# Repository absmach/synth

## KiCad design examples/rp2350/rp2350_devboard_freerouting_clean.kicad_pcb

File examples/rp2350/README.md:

# RP2350 routed example

## Latest regenerated run

The full-board reconstruction routes with the installed FreeRouting pipeline
on six layers. Local generated artifacts are under
`reproductions/rp2350-reconstructed/generated/`:

- `rp2350_devboard_reconstructed.synth` — reconstructed Synth source
- `rp2350_devboard_reconstructed.layout.toml` — recovered placement sidecar
- `rp2350_devboard_freerouted_6layer.kicad_pcb` — routed KiCad board
- `rp2350_devboard_freerouted_6layer.png` — rendered review image
- `freerouted-6layer-drc.rpt` — native KiCad DRC report

FreeRouting completed with **0 unrouted signal nets**. The DRC report still
contains 14 ground-zone island items and two footprint-library warnings; this
is not production sign-off until those items are reviewed.

`rp2350_devboard_freerouting_clean.kicad_pcb` is a pre-generated compact KiCad
review artifact.

Reference dimensions: approximately **84.5 × 73.1 mm**.

Open the [KiCad board](rp2350_devboard_freerouting_clean.kicad_pcb) for an
interactive review.

The companion DRC report records the current review state. The authoritative
KiCad check currently reports **80 DRC violations** and **18 unconnected
items**. The 18 unconnected entries are zone-to-zone ground-island reports,
not ordinary signal-pad pairs, but they are still violations. This is an
example and review fixture, not production sign-off; silkscreen and footprint
library warnings also require engineering review.

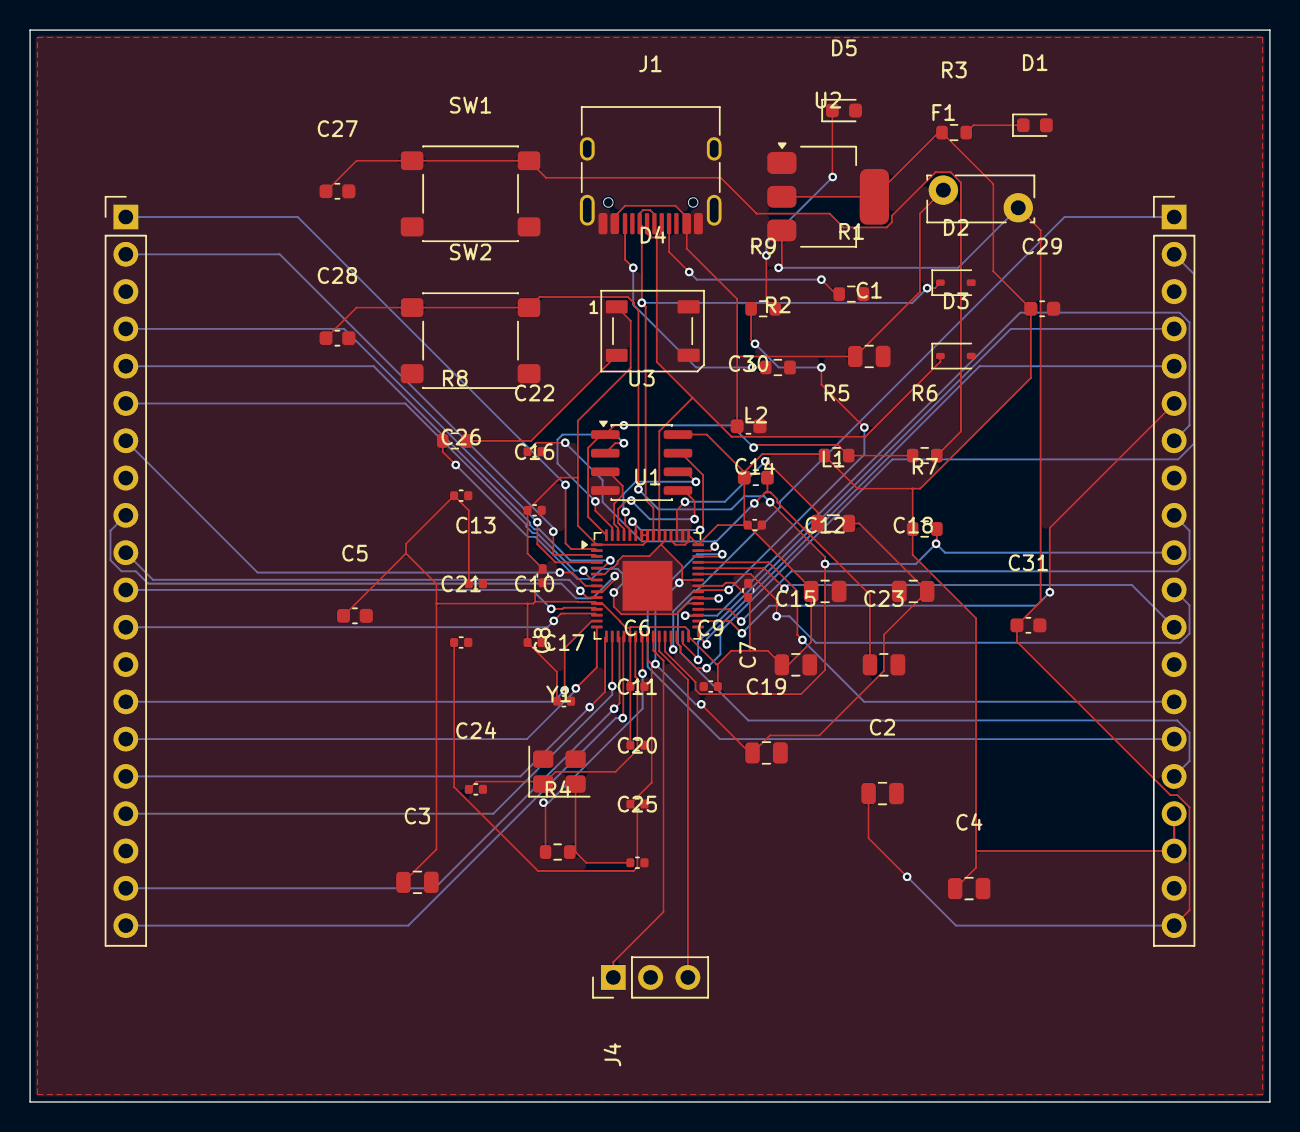
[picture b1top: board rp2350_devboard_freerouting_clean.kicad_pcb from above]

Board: 4 copper layers, 84.4 x 73.0 mm, 58 parts (0 on the bottom side), 57 nets.

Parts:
C1, C2, C3, C4, C12, C15, C18, C19, C23: c_generic_0805; C_0805_2012Metric
C5, C27, C28, C29, C30, C31: c_generic_0603; C_0603_1608Metric
C6, C7, C8, C9, C10, C11, C13, C14, C16, C17, C20, C21, C22, C24, C25, C26: c_generic_0402; C_0402_1005Metric
D1: led_green_0603; LED_0603_1608Metric
D2, D3: esd_usb; D_SOD-323
D4: ws2812b_5050; LED_WS2812B_PLCC4_5.0x5.0mm_P3.2mm
D5: led_red_0603; LED_0603_1608Metric
F1: polyfuse; Fuse_Bourns_MF-RG300
J1: usb_c_receptacle; USB_C_Receptacle_HRO_TYPE-C-31-M-12
J2, J3: header_1x20; PinHeader_1x20_P2.54mm_Vertical
J4: header_1x3; PinHeader_1x03_P2.54mm_Vertical
L1: l_generic_0805; L_0805_2012Metric
L2: ferrite_bead_0603; L_0603_1608Metric
R1, R2, R3, R4, R5, R6, R7, R8, R9: r_generic_0603; R_0603_1608Metric
SW1, SW2: spst_tactile; SW_SPST_PTS645Sx43SMTR92
U1: rp2350a; QFN-60-1EP_7x7mm_P0.4mm_EP3.4x3.4mm
U2: ams1117_3v3; SOT-223-3_TabPin2
U3: w25q128_qspi; SOIC-8_3.9x4.9mm_P1.27mm
Y1: xtal_generic; Crystal_SMD_3225-4Pin_3.2x2.5mm

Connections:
net_0: J1.A5, R1.1
net_1: C1.2, C2.2, C3.2, C4.2, C5.2, C6.2, C7.2, C8.2, C9.2, C10.2, C11.2, C12.2, C13.2, C14.2, C15.2, C16.2, C17.2, C18.2, C19.2, C20.2, C21.2, C22.2, C23.2, C24.2, C25.2, C26.2, C27.2, C28.2, C29.2, C30.2, C31.2, D1.2, D2.2, D3.2, D4.3, D4.4, D5.2, J1.A1, J1.A12, J1.B1, J1.B12, J1.SH, J2.3, J2.8, J2.13, J2.18, J3.3, J3.8, J3.13, J3.19, J4.2, R1.2, R2.2, SW1.2, SW2.2, U1.47, U1.61, U2.1, U3.4
net_2: J1.B5, R2.1
net_3: C1.1, C30.1, F1.1, J1.A4, J1.A9, J1.B4, J1.B9
net_4: C2.1, C31.1, F1.2, J3.20, U2.3
net_5: C3.1, C4.1, C5.1, C6.1, C7.1, C8.1, C9.1, C10.1, C11.1, C12.1, C13.1, C14.1, C15.1, C16.1, C17.1, C26.1, C29.1, D4.1, J3.17, J3.18, L2.1, R3.1, R5.1, R7.1, U1.1, U1.11, U1.20, U1.30, U1.38, U1.45, U1.46, U1.49, U1.53, U1.54, U2.2, U3.8
net_6: D1.1, R3.2
net_7: L1.1, U1.48
net_8: C18.1, C19.1, C20.1, C21.1, L1.2, U1.6, U1.23, U1.39, U1.50
net_9: C22.1, C23.1, L2.2, U1.44
net_10: C24.1, U1.21, Y1.1
net_11: R4.1, U1.22
net_12: C25.1, R4.2, Y1.2
net_13: R5.2, R6.1, U1.60, U3.1
net_14: U1.56, U3.6
net_15: U1.57, U3.5
net_16: U1.59, U3.2
net_17: U1.58, U3.3
net_18: U1.55, U3.7
net_19: C27.1, R6.2, SW1.1
net_20: C28.1, J3.10, R7.2, SW2.1, U1.26
net_21: D2.1, J1.A6, J1.B6, U1.52
net_22: D3.1, J1.A7, J1.B7, U1.51
net_23: R8.1, U1.35
net_24: D4.2, R8.2
net_25: R9.1, U1.37
net_26: D5.1, R9.2
net_27: J4.1, U1.24
net_28: J4.3, U1.25
net_29: J2.1, U1.2
net_30: J2.2, U1.3
net_31: J2.4, U1.4
net_32: J2.5, U1.5
net_33: J2.6, U1.7
net_34: J2.7, U1.8
net_35: J2.9, U1.9
net_36: J2.10, U1.10
net_37: J2.11, U1.12
net_38: J2.12, U1.13
net_39: J2.14, U1.14
net_40: J2.15, U1.15
net_41: J2.16, U1.16
net_42: J2.17, U1.17
net_43: J2.19, U1.18
net_44: J2.20, U1.19
net_45: J3.1, U1.27
net_46: J3.2, U1.28
net_47: J3.4, U1.29
net_48: J3.5, U1.31
net_49: J3.6, U1.32
net_50: J3.7, U1.33
net_51: J3.9, U1.34
net_52: J3.11, U1.40
net_53: J3.12, U1.41
net_54: J3.14, U1.42
net_55: J3.15, U1.43
net_56: J3.16, U1.36

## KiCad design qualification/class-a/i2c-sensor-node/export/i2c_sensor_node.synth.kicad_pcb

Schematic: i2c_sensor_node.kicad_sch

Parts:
C1, C2, C4: 10uF; C_0805_2012Metric
C3: 47uF; CP_EIA-3528-21_Kemet-B
C5, C6, C8, C10, C11, C12: 100nF; C_0603_1608Metric
C7: 4.7uF; C_0603_1608Metric
D1, D14: 1N5819; D_SOD-123; MPN 1N5819HW-7-F; LCSC C82544
D4: PTVS6V0S1UR; Nexperia_CFP3_SOD-123W; MPN PTVS6V0S1UR
D7, D8, D9, D10, D11, D12, D13, D19, D20, D21, D22, D23, D24: 3.3V zener; D_SOD-123
D15: GREEN; LED_0603_1608Metric; MPN LTST-C190KGKT
F1: 0.5A hold; Fuse_1812_4532Metric
H2, H3: (no value); MountingHole_2.5mm
J1: JST S2B-XH-A-1; JST_XH_S2B-XH-A-1_1x02_P2.50mm_Horizontal
J3: JST S4B-PH-K-S; JST_PH_S4B-PH-K_1x04_P2.00mm_Horizontal
J4: SWD; PinHeader_1x05_P2.54mm_Vertical
J5: GPIO; PinHeader_1x12_P2.54mm_Vertical
R3: 10k; R_0603_1608Metric
R9, R10: 4.7k; R_0603_1608Metric
R11, R15, R16, R17, R18, R19, R20, R21, R22: 330; R_0603_1608Metric
R12: 1k; R_0603_1608Metric
R13, R14: 100; R_0603_1608Metric
R23: 100; R_0805_2012Metric
R24: 680; R_0603_1608Metric
SW1: RESET; SW_SPST_PTS645Sx43SMTR92
U1: AMS1117-3.3; SOT-223-3_TabPin2; MPN AMS1117-3.3; LCSC C6186
U2: STM32G030F6P6; TSSOP-20_4.4x6.5mm_P0.65mm; MPN STM32G030F6P6
U3: BME680; Bosch_LGA-8_3x3mm_P0.8mm_ClockwisePinNumbering; MPN BME680
U5: 24LC256-I/SN; SOIC-8_3.9x4.9mm_P1.27mm; MPN 24LC256-I/SN; LCSC C411625

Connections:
3V3_REF: J3.4, J4.1, J5.1, R23.2
+3V3: C3.1, C4.1, C5.1, C6.1, C7.1, C10.1, C11.1, C12.1, D14.2 (A), R3.1, R9.1, R10.1, R24.1, U1.2 (VO), U2.4 (VDD), U3.2 (CSB), U3.6 (VDDIO), U3.8 (VDD), U5.8 (VCC)
+5V_PROT: C1.1, C2.1, D1.1 (K), D4.1 (K), U1.3 (VI)
GND: C1.2, C2.2, C3.2, C4.2, C5.2, C6.2, C7.2, C8.2, C10.2, C11.2, C12.2, D4.2 (A), D7.2 (A), D8.2 (A), D9.2 (A), D10.2 (A), D11.2 (A), D12.2 (A), D13.2 (A), D15.1 (K), D19.2 (A), D20.2 (A), D21.2 (A), D22.2 (A), D23.2 (A), D24.2 (A), J1.2, J3.1, J4.4, J5.2, J5.6, J5.10, SW1.2, U1.1 (GND), U2.5 (VSS), U3.1 (GND), U3.5 (SDO), U3.7 (GND), U5.1 (A0), U5.2 (A1), U5.3 (A2), U5.4 (GND), U5.7 (WP)
GPIO_PA0: J5.3, R15.2
GPIO_PA0_MCU: D10.1 (K), R15.1, U2.7 (PA0)
GPIO_PA1: J5.4, R16.2
GPIO_PA1_MCU: D20.1 (K), R16.1, U2.8 (PA1)
GPIO_PA4: J5.5, R17.2
GPIO_PA4_MCU: D11.1 (K), R17.1, U2.11 (PA4)
GPIO_PA5: J5.7, R18.2
GPIO_PA5_MCU: D21.1 (K), R18.1, U2.12 (PA5)
GPIO_PA6: J5.8, R19.2
GPIO_PA6_MCU: D12.1 (K), R19.1, U2.13 (PA6)
GPIO_PA7: J5.9, R20.2
GPIO_PA7_MCU: D22.1 (K), R20.1, U2.14 (PA7)
GPIO_PB0: J5.11, R21.2
GPIO_PB0_MCU: D13.1 (K), R21.1, U2.15 (PA8/PB0/PB1/PB2)
GPIO_PB9: J5.12, R22.2
GPIO_PB9_MCU: D23.1 (K), R22.1, U2.2 (PB9/PC14)
I2C_SCL: R10.2, U2.20 (PB3/PB4/PB5/PB6), U3.4 (SCK), U5.6 (SCL)
I2C_SDA: R9.2, U2.1 (PB7/PB8), U3.3 (SDI), U5.5 (SDA)
LED_PWR: D15.2 (A), R24.2
NRST: C8.1, D19.1 (K), J4.5, R3.2, SW1.1, U2.6 (NRST)
REF_D: D14.1 (K), R23.1
SWCLK: D9.1 (K), J4.3, R14.2
SWCLK_MCU: R14.1, U2.19 (PA14/PA15)
SWDIO: D8.1 (K), J4.2, R13.2
SWDIO_MCU: R13.1, U2.18 (PA13)
U2_RX: D24.1 (K), R12.1, U2.10 (PA3)
U2_TX: D7.1 (K), R11.1, U2.9 (PA2)
UART_RX: J3.3, R12.2
UART_TX: J3.2, R11.2
VIN_5V_FUSED: D1.2 (A), F1.2
VIN_5V_RAW: F1.1, J1.1

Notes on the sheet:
5V INPUT: FUSE THEN DIODE
3V3 REGULATOR
STM32G030 MCU
I2C SENSING
UART BREAKOUT
GPIO HEADER
MOUNTING
J1 pin 1 = +5 V, pin 2 = GND (JST XHP-2). Fuse first, then the
reverse-polarity diode D1.
D4 clamps transients on +5V_PROT, behind D1 so a reversed supply never
forward-biases it.
AMS1117 tab is VOUT. Load budget 100 mA: P = (5.0 - 3.3) x 0.1 A =
0.17 W, thetaJA 90 C/W gives a 15 C rise (125 C limit).
LED (VF 1.9 to 2.4 V): 1.3 to 2.1 mA through 680 R. C3 is 47 uF
tantalum (22 uF required).
J4: 1 = 3V3_REF, 2 = SWDIO, 3 = SWCLK, 4 = GND, 5 = NRST. PA14 is
SWCLK and BOOT0.
D8, D9, D19 are 3.3 V zeners; a 5 V fault through 100 R is (5 - 3.3) /
100 = 17 mA, 56 mW.
BME680 SDO low = 0x76, CSB high = I2C. 24LC256 A2:A0 low = 0x50. No
collision.
One pull-up pair, 4.7k each, for the whole bus.
J3: 1 GND, 2 UART_TX, 3 UART_RX, 4 3V3_REF (3 mA max). Host logic 3.3
V to 5 V.
D7, D24 are 3.3 V zeners behind 330 R and 1 k: a 5 V fault is 5.2 mA
(17 mW) and 1.7 mA (5.6 mW).
J5: 1 3V3_REF, 2 GND, 3 PA0, 4 PA1, 5 PA4, 6 GND, 7 PA5, 8 PA6, 9 PA7,
10 GND, 11 PB0, 12 PB9.
D10..D13, D20..D23: one 3.3 V zener per line behind 330 R; a 5 V fault
is 5.2 mA, 17 mW. 3V3_REF is +3V3 through D14 and 100 R, 3 mA max.
H2, H3: two M2.5 non-plated mounting holes at opposite (diagonal)
corners.

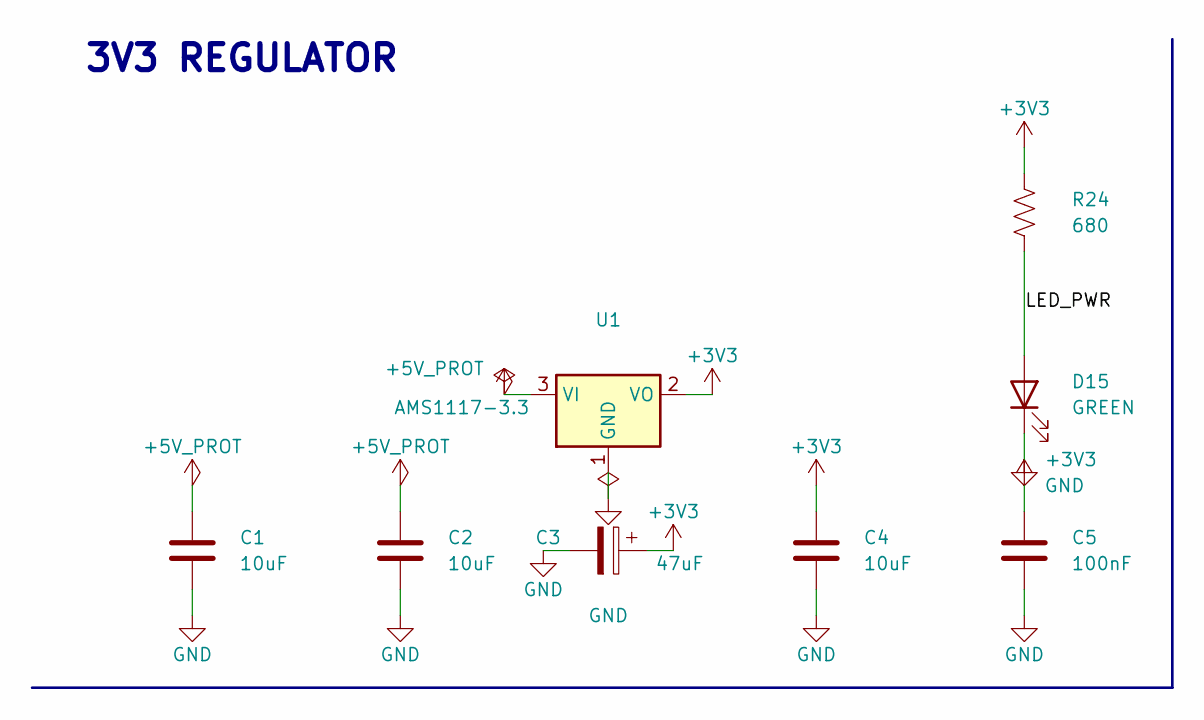
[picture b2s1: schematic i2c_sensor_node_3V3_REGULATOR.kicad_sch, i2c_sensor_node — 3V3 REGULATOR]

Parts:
C1, C2, C4: 10uF; C_0805_2012Metric
C3: 47uF; CP_EIA-3528-21_Kemet-B
C5: 100nF; C_0603_1608Metric
D15: GREEN; LED_0603_1608Metric; MPN LTST-C190KGKT
R24: 680; R_0603_1608Metric
U1: AMS1117-3.3; SOT-223-3_TabPin2; MPN AMS1117-3.3; LCSC C6186

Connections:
+3V3: C3.1, C4.1, C5.1, R24.1, U1.2 (VO); also elsewhere on the board
+5V_PROT: C1.1, C2.1, U1.3 (VI); also elsewhere on the board
GND: C1.2, C2.2, C3.2, C4.2, C5.2, D15.1 (K), U1.1 (GND); also elsewhere on the board
LED_PWR: D15.2 (A), R24.2

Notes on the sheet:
3V3 REGULATOR

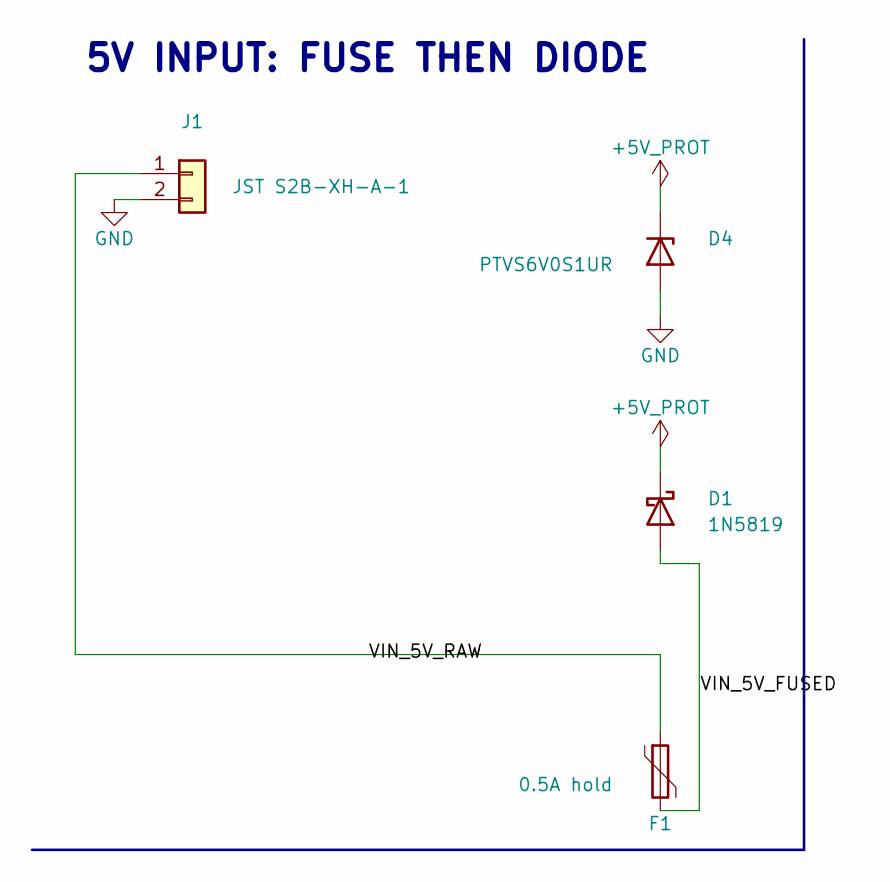
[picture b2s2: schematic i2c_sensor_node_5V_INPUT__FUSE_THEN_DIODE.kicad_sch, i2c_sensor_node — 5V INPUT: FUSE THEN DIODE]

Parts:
D1: 1N5819; D_SOD-123; MPN 1N5819HW-7-F; LCSC C82544
D4: PTVS6V0S1UR; Nexperia_CFP3_SOD-123W; MPN PTVS6V0S1UR
F1: 0.5A hold; Fuse_1812_4532Metric
J1: JST S2B-XH-A-1; JST_XH_S2B-XH-A-1_1x02_P2.50mm_Horizontal

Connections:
+5V_PROT: D1.1 (K), D4.1 (K); also elsewhere on the board
GND: D4.2 (A), J1.2; also elsewhere on the board
VIN_5V_FUSED: D1.2 (A), F1.2
VIN_5V_RAW: F1.1, J1.1

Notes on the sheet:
5V INPUT: FUSE THEN DIODE

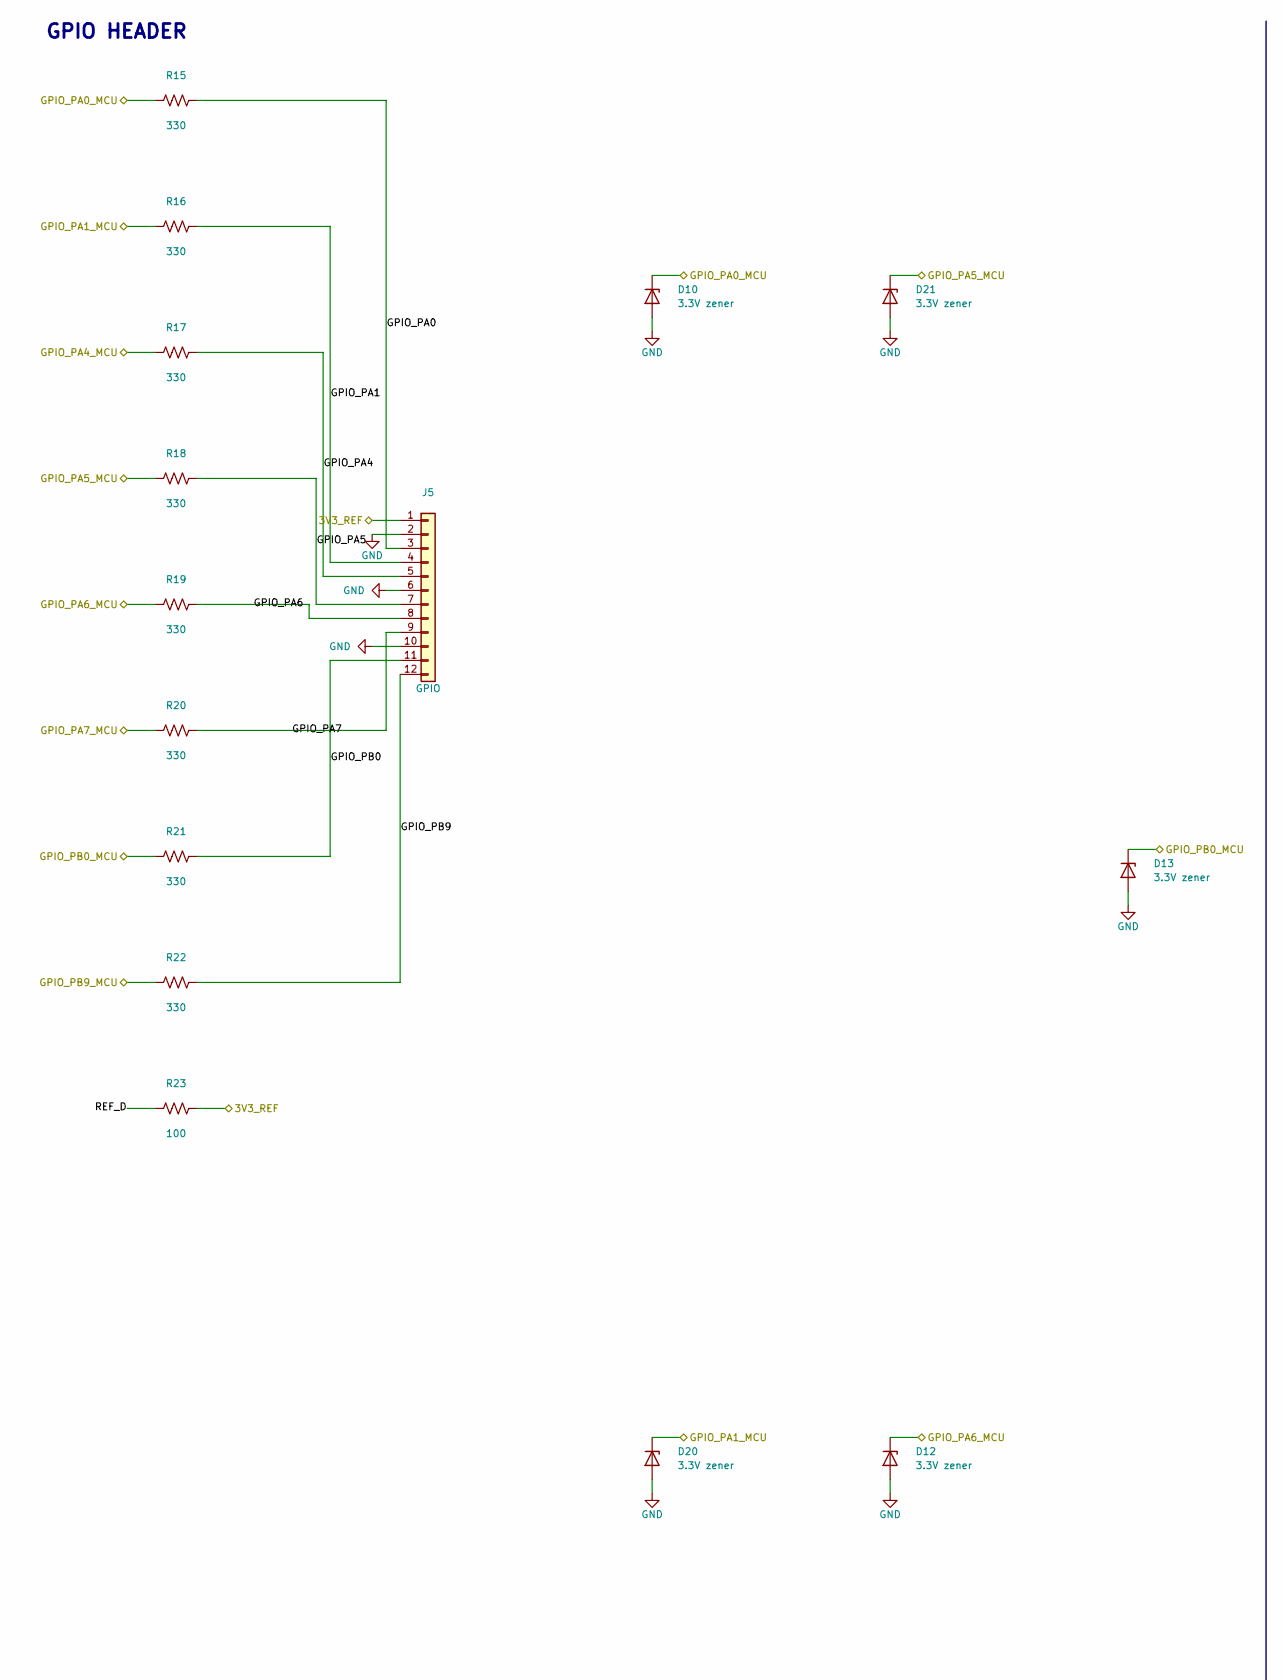
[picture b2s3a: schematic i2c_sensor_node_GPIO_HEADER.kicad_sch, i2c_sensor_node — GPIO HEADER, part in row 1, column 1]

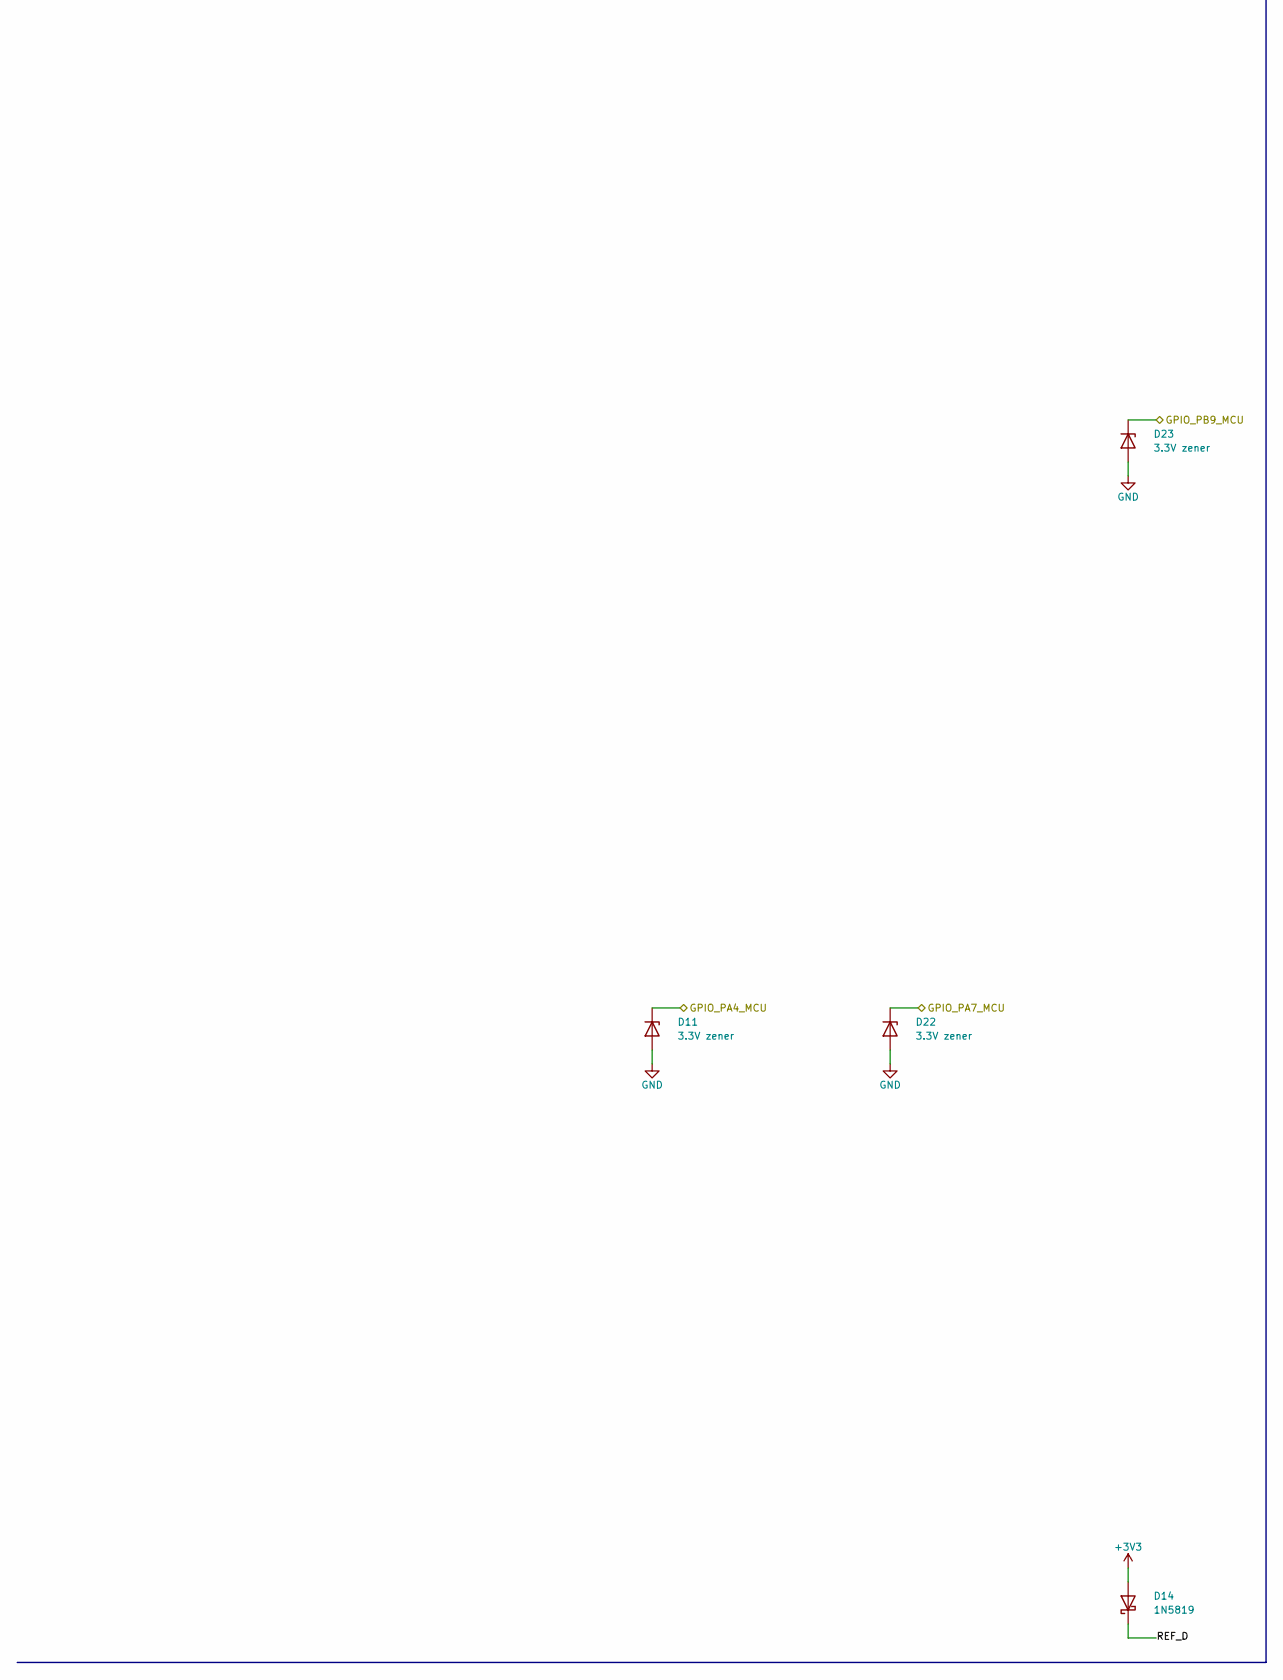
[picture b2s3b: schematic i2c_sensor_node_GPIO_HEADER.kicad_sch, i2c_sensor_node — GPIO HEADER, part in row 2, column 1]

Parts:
D10, D11, D12, D13, D20, D21, D22, D23: 3.3V zener; D_SOD-123
D14: 1N5819; D_SOD-123; MPN 1N5819HW-7-F; LCSC C82544
J5: GPIO; PinHeader_1x12_P2.54mm_Vertical
R15, R16, R17, R18, R19, R20, R21, R22: 330; R_0603_1608Metric
R23: 100; R_0805_2012Metric

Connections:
3V3_REF: J5.1, R23.2; also elsewhere on the board
+3V3: D14.2 (A); also elsewhere on the board
GND: D10.2 (A), D11.2 (A), D12.2 (A), D13.2 (A), D20.2 (A), D21.2 (A), D22.2 (A), D23.2 (A), J5.2, J5.6, J5.10; also elsewhere on the board
GPIO_PA0: J5.3, R15.2
GPIO_PA0_MCU: D10.1 (K), R15.1; also elsewhere on the board
GPIO_PA1: J5.4, R16.2
GPIO_PA1_MCU: D20.1 (K), R16.1; also elsewhere on the board
GPIO_PA4: J5.5, R17.2
GPIO_PA4_MCU: D11.1 (K), R17.1; also elsewhere on the board
GPIO_PA5: J5.7, R18.2
GPIO_PA5_MCU: D21.1 (K), R18.1; also elsewhere on the board
GPIO_PA6: J5.8, R19.2
GPIO_PA6_MCU: D12.1 (K), R19.1; also elsewhere on the board
GPIO_PA7: J5.9, R20.2
GPIO_PA7_MCU: D22.1 (K), R20.1; also elsewhere on the board
GPIO_PB0: J5.11, R21.2
GPIO_PB0_MCU: D13.1 (K), R21.1; also elsewhere on the board
GPIO_PB9: J5.12, R22.2
GPIO_PB9_MCU: D23.1 (K), R22.1; also elsewhere on the board
REF_D: D14.1 (K), R23.1

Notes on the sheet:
GPIO HEADER

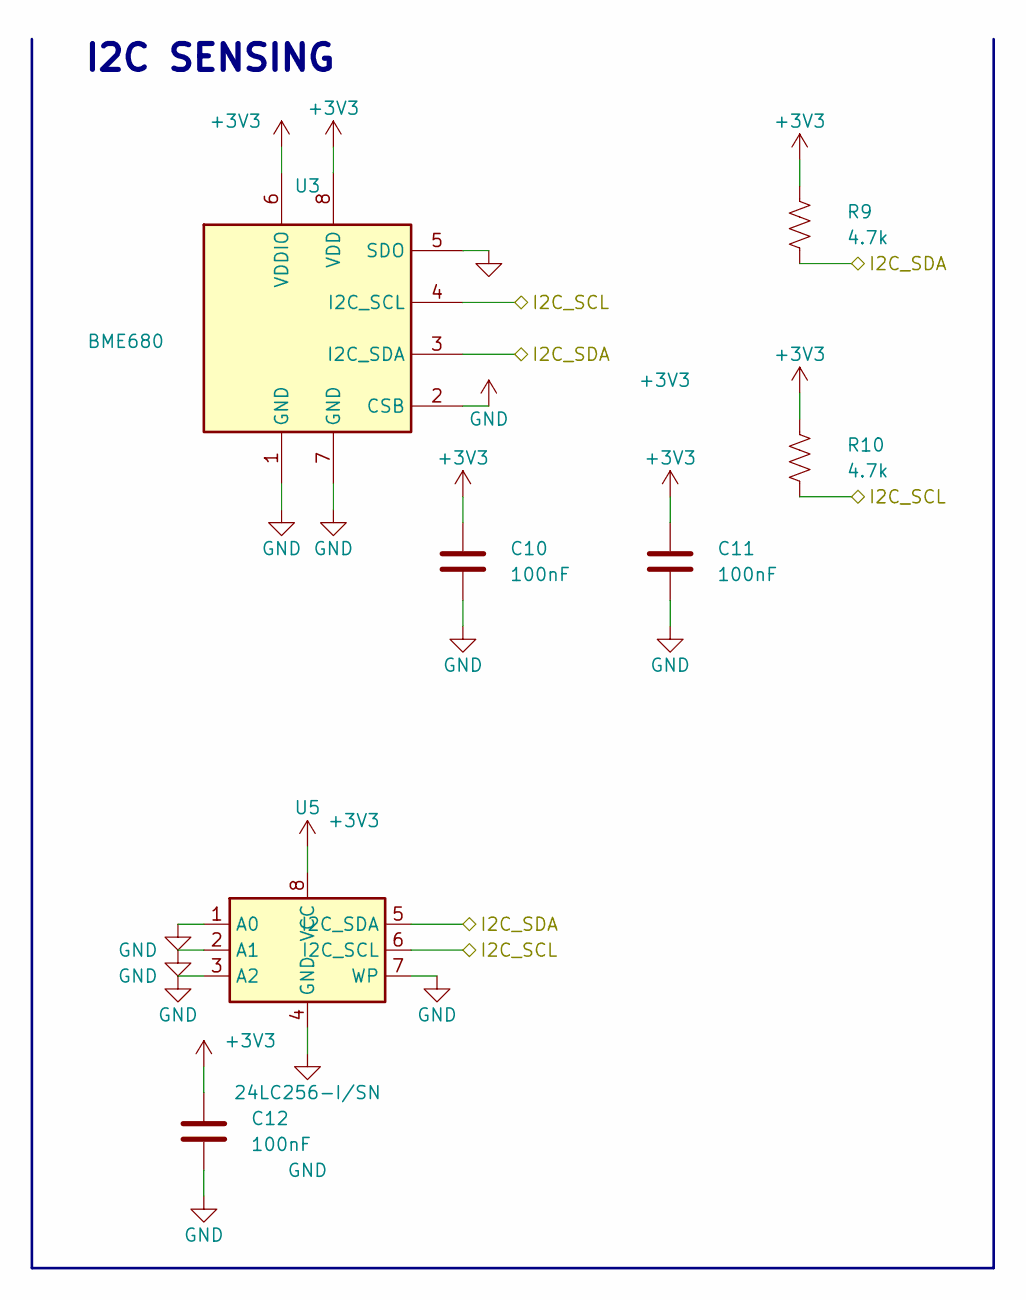
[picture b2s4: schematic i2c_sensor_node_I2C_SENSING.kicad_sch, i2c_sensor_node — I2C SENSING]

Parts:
C10, C11, C12: 100nF; C_0603_1608Metric
R9, R10: 4.7k; R_0603_1608Metric
U3: BME680; Bosch_LGA-8_3x3mm_P0.8mm_ClockwisePinNumbering; MPN BME680
U5: 24LC256-I/SN; SOIC-8_3.9x4.9mm_P1.27mm; MPN 24LC256-I/SN; LCSC C7611

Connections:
+3V3: C10.1, C11.1, C12.1, R9.1, R10.1, U3.2 (CSB), U3.6 (VDDIO), U3.8 (VDD), U5.8 (VCC); also elsewhere on the board
GND: C10.2, C11.2, C12.2, U3.1 (GND), U3.5 (SDO), U3.7 (GND), U5.1 (A0), U5.2 (A1), U5.3 (A2), U5.4 (GND), U5.7 (WP); also elsewhere on the board
I2C_SCL: R10.2, U3.4 (SCK), U5.6 (SCL); also elsewhere on the board
I2C_SDA: R9.2, U3.3 (SDI), U5.5 (SDA); also elsewhere on the board

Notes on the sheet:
I2C SENSING

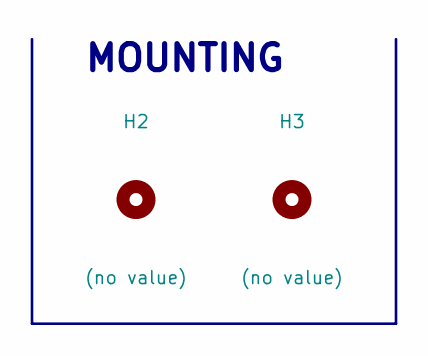
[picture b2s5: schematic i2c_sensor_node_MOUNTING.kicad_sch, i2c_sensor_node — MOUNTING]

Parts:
H2, H3: (no value); MountingHole_2.5mm

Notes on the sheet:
MOUNTING

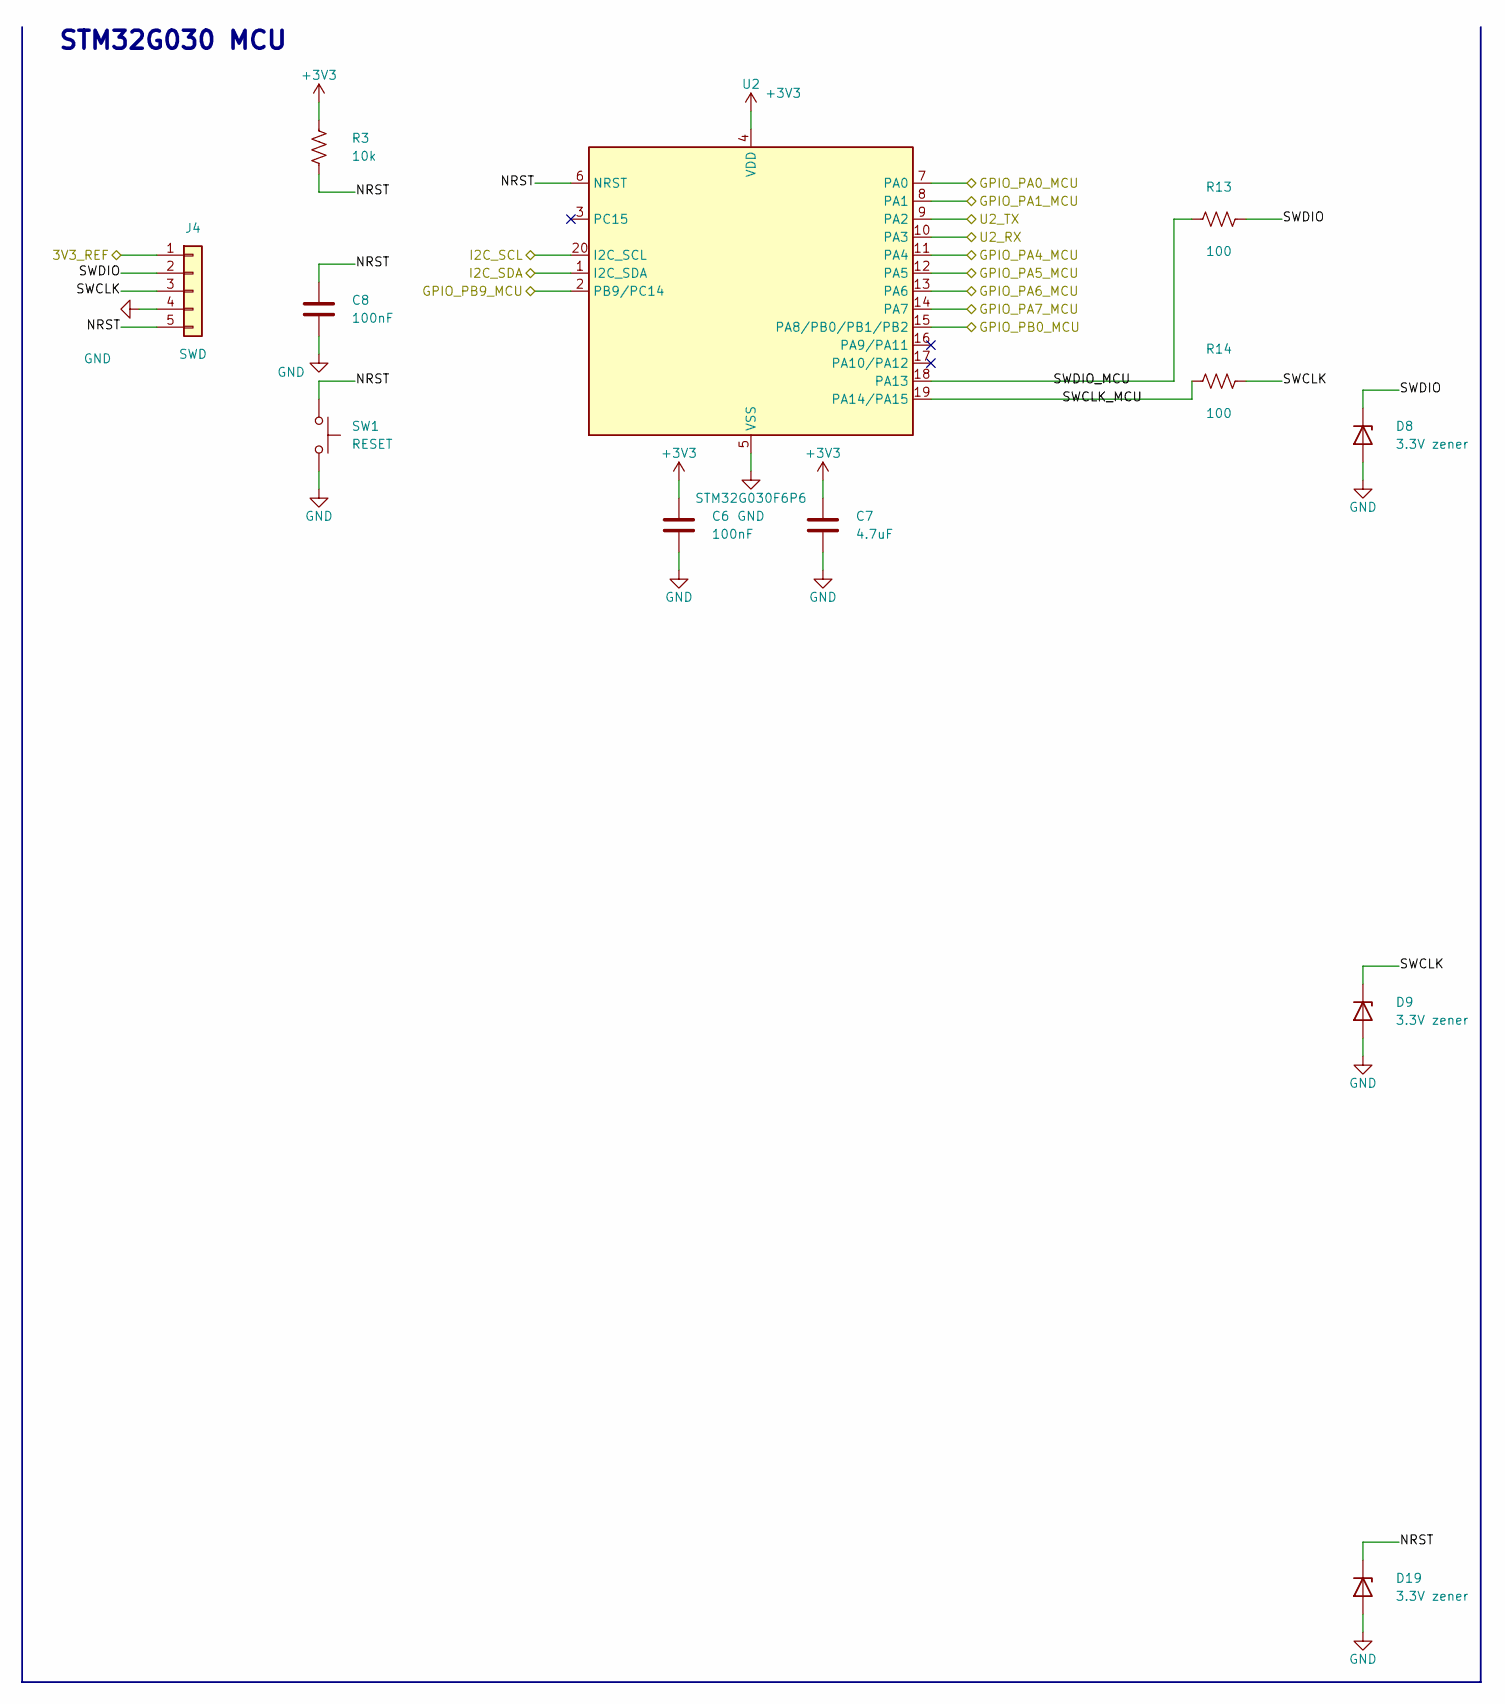
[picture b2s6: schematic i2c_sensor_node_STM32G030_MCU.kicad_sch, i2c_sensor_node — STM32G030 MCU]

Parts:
C6, C8: 100nF; C_0603_1608Metric
C7: 4.7uF; C_0603_1608Metric
D8, D9, D19: 3.3V zener; D_SOD-123
J4: SWD; PinHeader_1x05_P2.54mm_Vertical
R3: 10k; R_0603_1608Metric
R13, R14: 100; R_0603_1608Metric
SW1: RESET; SW_SPST_PTS645Sx43SMTR92
U2: STM32G030F6P6; TSSOP-20_4.4x6.5mm_P0.65mm; MPN STM32G030F6P6

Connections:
3V3_REF: J4.1; also elsewhere on the board
+3V3: C6.1, C7.1, R3.1, U2.4 (VDD); also elsewhere on the board
GND: C6.2, C7.2, C8.2, D8.2 (A), D9.2 (A), D19.2 (A), J4.4, SW1.2, U2.5 (VSS); also elsewhere on the board
GPIO_PA0_MCU: U2.7 (PA0); also elsewhere on the board
GPIO_PA1_MCU: U2.8 (PA1); also elsewhere on the board
GPIO_PA4_MCU: U2.11 (PA4); also elsewhere on the board
GPIO_PA5_MCU: U2.12 (PA5); also elsewhere on the board
GPIO_PA6_MCU: U2.13 (PA6); also elsewhere on the board
GPIO_PA7_MCU: U2.14 (PA7); also elsewhere on the board
GPIO_PB0_MCU: U2.15 (PA8/PB0/PB1/PB2); also elsewhere on the board
GPIO_PB9_MCU: U2.2 (PB9/PC14); also elsewhere on the board
I2C_SCL: U2.20 (PB3/PB4/PB5/PB6); also elsewhere on the board
I2C_SDA: U2.1 (PB7/PB8); also elsewhere on the board
NRST: C8.1, D19.1 (K), J4.5, R3.2, SW1.1, U2.6 (NRST)
SWCLK: D9.1 (K), J4.3, R14.2
SWCLK_MCU: R14.1, U2.19 (PA14/PA15)
SWDIO: D8.1 (K), J4.2, R13.2
SWDIO_MCU: R13.1, U2.18 (PA13)
U2_RX: U2.10 (PA3); also elsewhere on the board
U2_TX: U2.9 (PA2); also elsewhere on the board

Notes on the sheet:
STM32G030 MCU

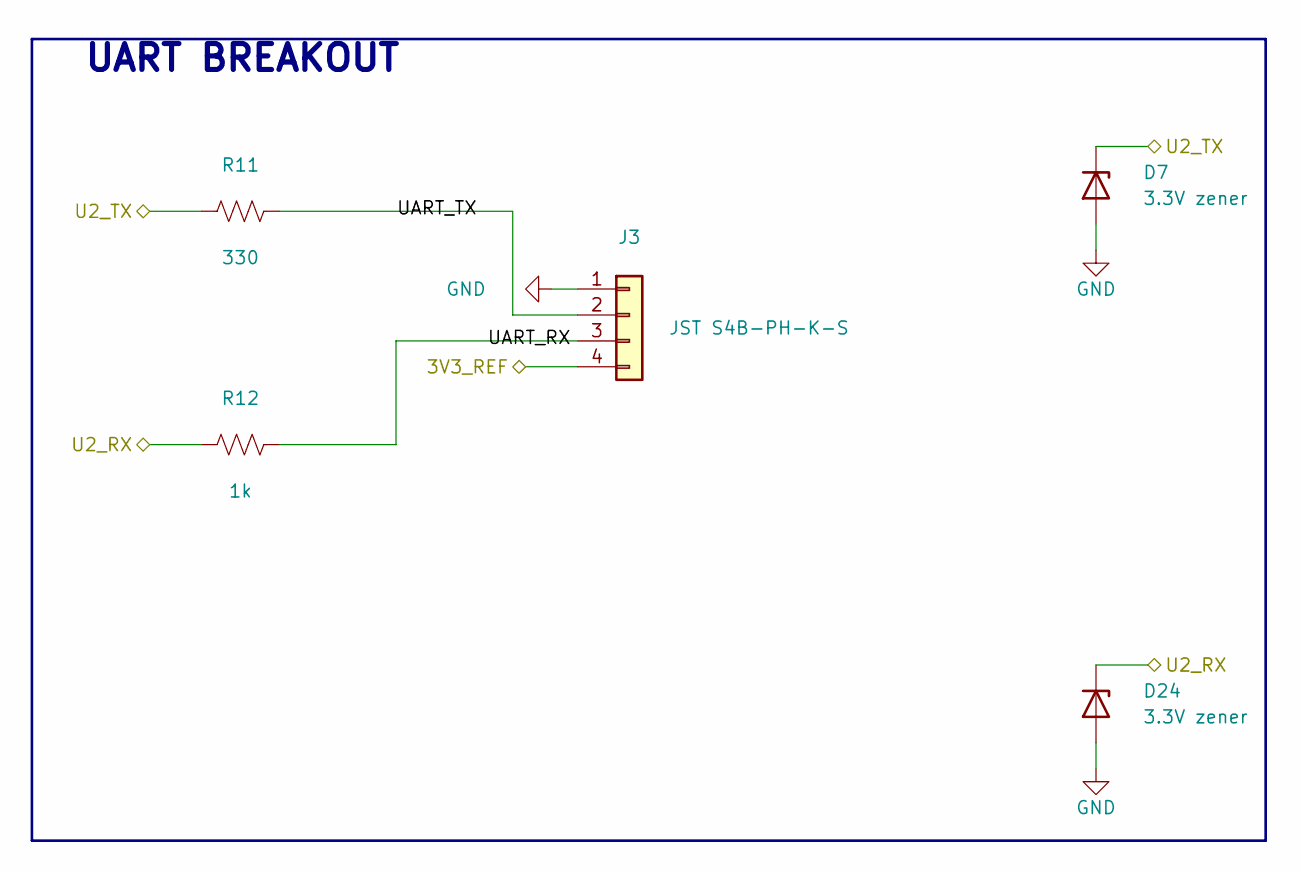
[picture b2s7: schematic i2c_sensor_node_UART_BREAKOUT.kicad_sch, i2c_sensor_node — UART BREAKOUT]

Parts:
D7, D24: 3.3V zener; D_SOD-123
J3: JST S4B-PH-K-S; JST_PH_S4B-PH-K_1x04_P2.00mm_Horizontal
R11: 330; R_0603_1608Metric
R12: 1k; R_0603_1608Metric

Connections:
3V3_REF: J3.4; also elsewhere on the board
GND: D7.2 (A), D24.2 (A), J3.1; also elsewhere on the board
U2_RX: D24.1 (K), R12.1; also elsewhere on the board
U2_TX: D7.1 (K), R11.1; also elsewhere on the board
UART_RX: J3.3, R12.2
UART_TX: J3.2, R11.2

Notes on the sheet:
UART BREAKOUT
